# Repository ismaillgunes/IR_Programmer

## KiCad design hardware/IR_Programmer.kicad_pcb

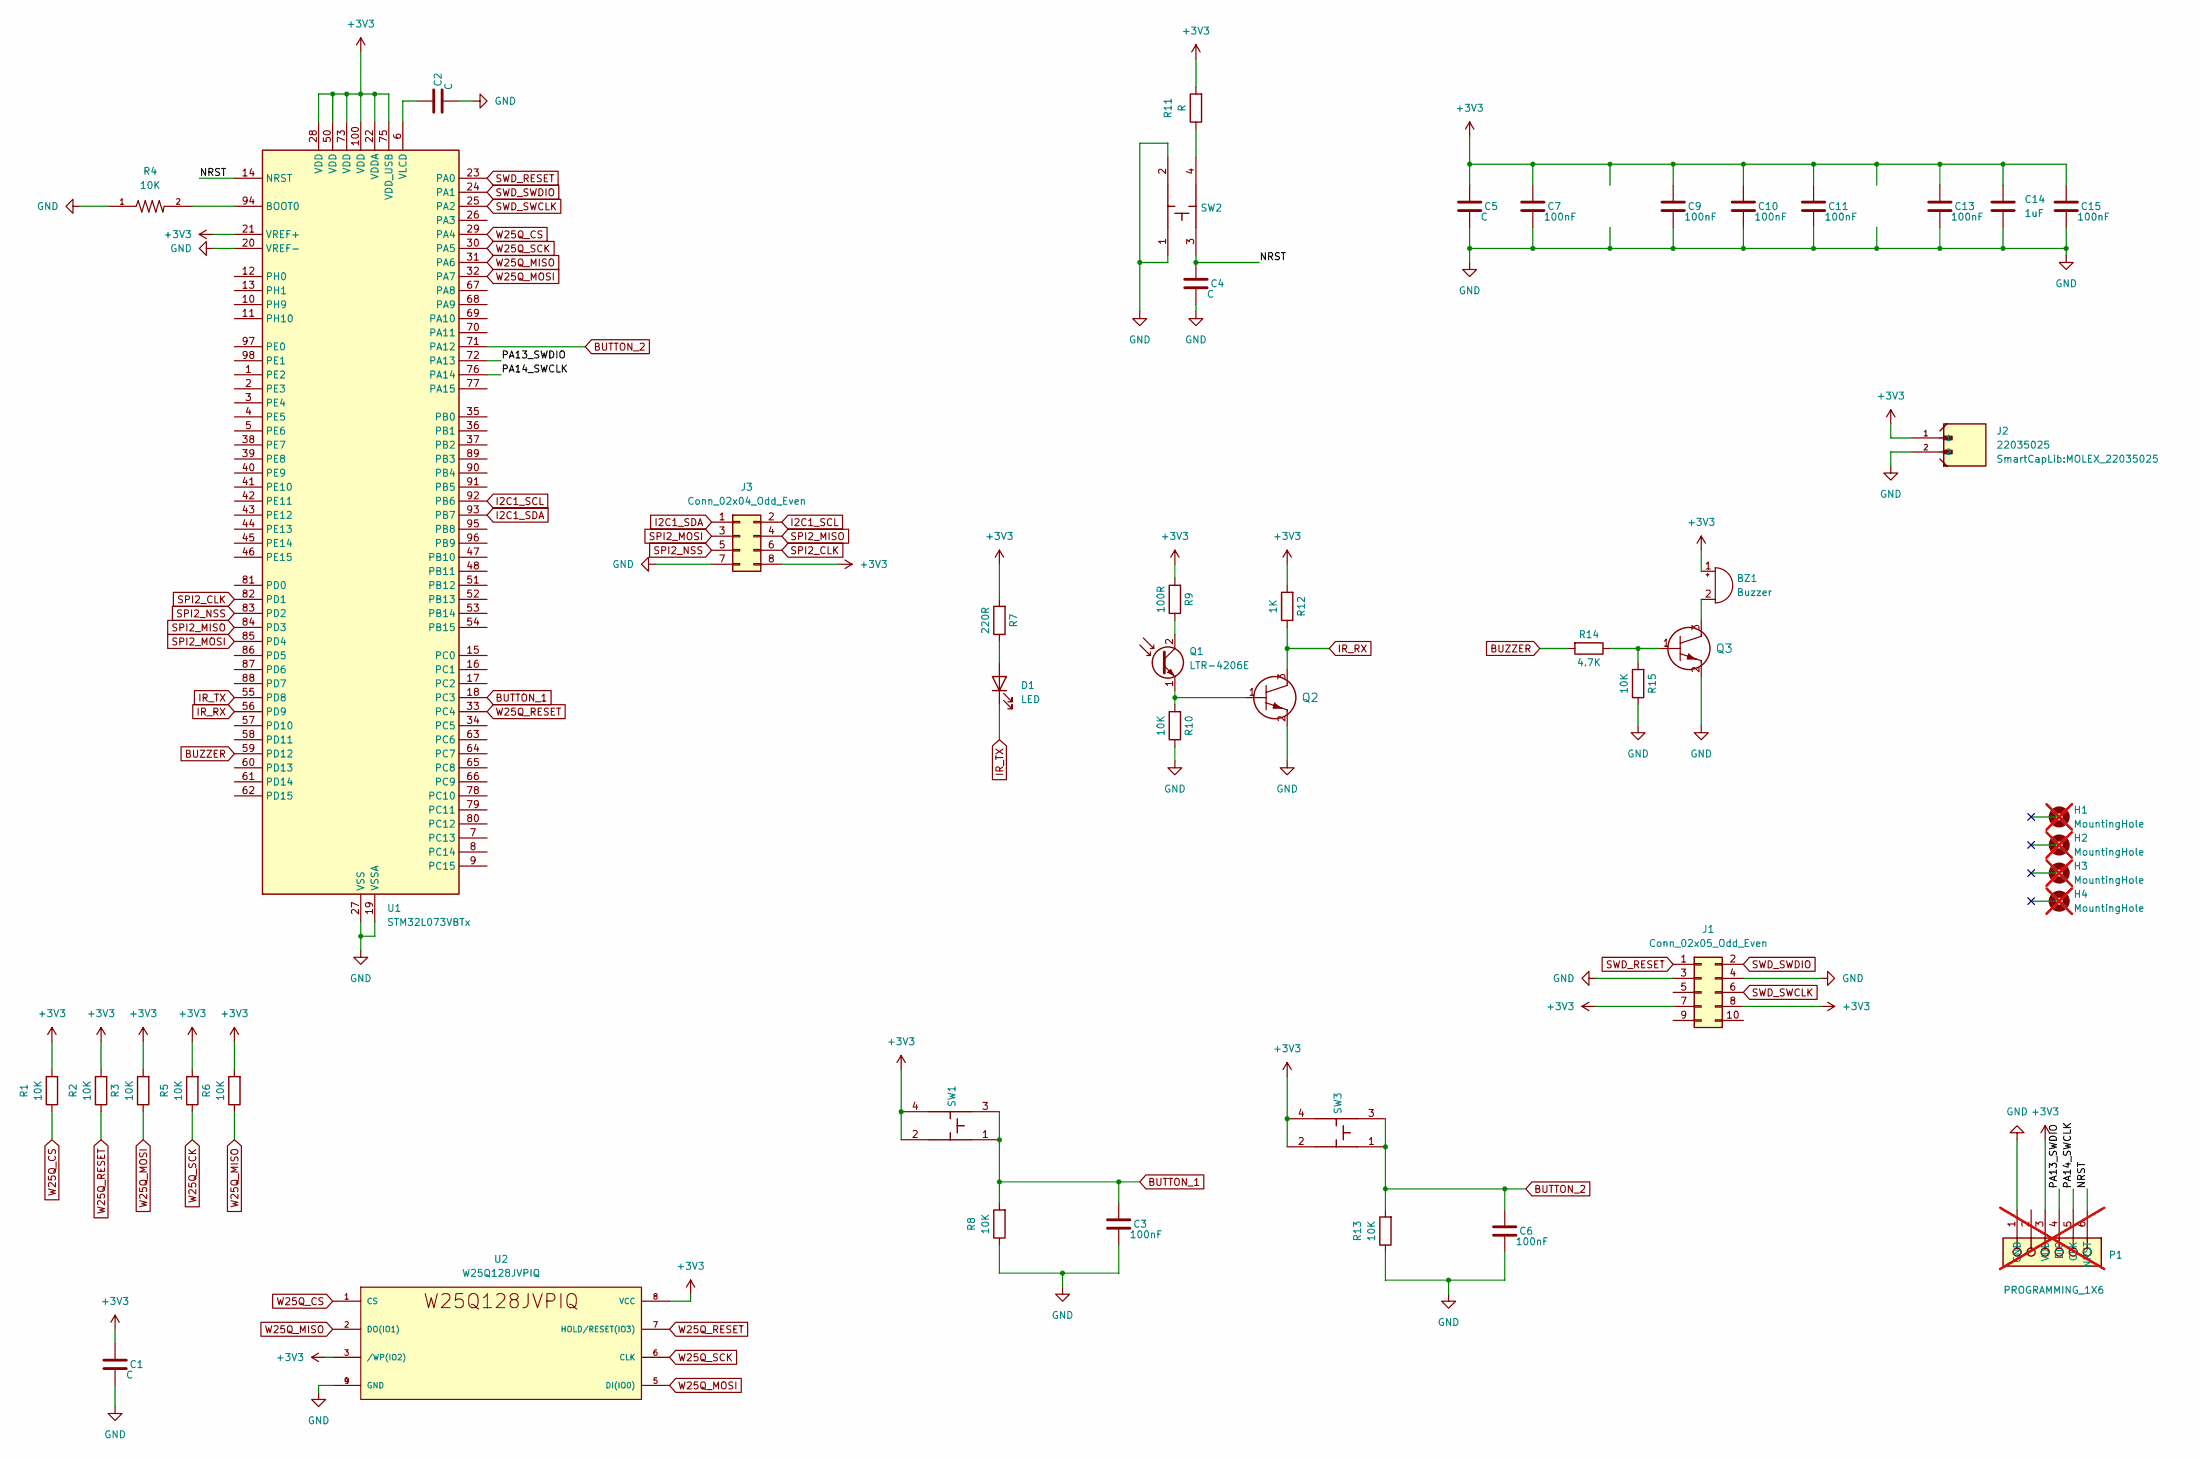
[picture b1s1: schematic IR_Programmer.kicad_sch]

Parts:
BZ1: Buzzer; Buzzer_12x9.5RM7.6
C1, C2, C4: C; C_0603_1608Metric; Manufacturer Part Num. CC0603KRX7R9BB104
C3, C6, C7, C9, C10, C11, C13, C15: 100nF; C_0603_1608Metric; Manufacturer Part Num. CC0603KRX7R9BB104
C5: C; C_0603_1608Metric; Manufacturer Part Num. CL10A106MQ8NNNC
C14: 1uF; C_0603_1608Metric; Manufacturer Part Number CC0603KRX7R7BB105
D1: LED; D_T-1_P2.54mm_Vertical_AnodeUp
H1, H2, H3, H4: MountingHole; MountingHole_3.5mm_Pad; not fitted
J1: Conn_02x05_Odd_Even; PinHeader_2x05_P2.54mm_Vertical
J2: 22035025; MOLEX_22035025; PARTREV A
J3: Conn_02x04_Odd_Even; PinHeader_2x04_P2.54mm_Vertical
P1: PROGRAMMING_1X6; Programming Connection; not fitted
Q1: LTR-4206E; D_T-1_P2.54mm_Vertical_AnodeUp
Q2, Q3: MMBT3904-TP; SOT-23-3
R1, R2, R3, R5, R6, R8, R10, R13, R15: 10K; R_0603_1608Metric; Manufacturer Part Num. RC0603FR-0710KL
R4: 10K; RESC1607X60N
R7: 220R; R_0603_1608Metric; Manufacturer Part Num. RC0603FR-07220RL
R9: 100R; R_0603_1608Metric; Manufacturer Part Num. RC0603FR-07100RL
R11: R; R_0603_1608Metric; Manufacturer Part Num. RC0603FR-0710KL
R12: 1K; R_0603_1608Metric; Manufacturer Part Num. RC0603FR-071KL
R14: 4.7K; R_0603_1608Metric; Manufacturer Part Num. RC0603FR-074K7L
SW1, SW3: DS1042-03-1-8-KKR-160-10; MANUFACTURER PART NUMBER DS1042-03-1-8-KKR-160-10
SW2: DS1042-07-1-1KRR16008; SW_TS24-62-14-BL-200-SMT-TR-67; CURRENT RATING 50mA; MANUFACTURER PART NUMBER DS1042-07-1-1KRR16008
U1: STM32L073VBTx; LQFP-100_14x14mm_P0.5mm
U2: W25Q128JVPIQ; Manufacturer Part Num. W25Q128JVPIQ

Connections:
+3V3: BZ1.1 (+), C1.1, C5.1, C7.1, C9.1, C10.1, C11.1, C13.1, C14.1, C15.1, J1.7, J1.8, J2.1, J3.8, P1.3 (VDD), R1.2, R2.2, R3.2, R5.2, R6.2, R7.2, R9.2, R11.2, R12.2, SW1.2, SW1.4, SW3.2, SW3.4, U1.21 (VREF+), U1.22 (VDDA), U1.28 (VDD), U1.50 (VDD), U1.73 (VDD), U1.75 (VDD_USB), U1.100 (VDD), U2.3 (/WP(IO2)), U2.8 (VCC)
/NRST: C4.1, P1.6 (NRST), SW2.3, U1.14 (NRST)
/PA13_SWDIO: P1.4 (DIO), U1.72 (PA13)
/PA14_SWCLK: P1.5 (CLK), U1.76 (PA14)
BUTTON_1: C3.1, R8.2, SW1.1, SW1.3, U1.18 (PC3)
BUTTON_2: C6.1, R13.2, SW3.1, SW3.3, U1.71 (PA12)
BUZZER: R14.2, U1.59 (PD12)
GND: C1.2, C2.2, C3.2, C4.2, C5.2, C6.2, C7.2, C9.2, C10.2, C11.2, C13.2, C14.2, C15.2, J1.3, J1.4, J2.2, J3.7, P1.1 (GND), Q2.2, Q3.2, R4.1, R8.1, R10.1, R13.1, R15.1, SW2.1, SW2.2, U1.19 (VSSA), U1.20 (VREF-), U1.27 (VSS), U1.49 (VSS), U1.74 (VSS), U1.99 (VSS), U2.4 (GND), U2.9 (GND)
I2C1_SCL: J3.2, U1.92 (PB6)
I2C1_SDA: J3.1, U1.93 (PB7)
IR_RX: Q2.3, R12.1, U1.56 (PD9)
IR_TX: D1.1 (K), U1.55 (PD8)
unnamed: BZ1.2 (-), Q3.3
unnamed: D1.2 (A), R7.1
unnamed: Q1.2 (C), R9.1
unnamed: Q1.1 (E), Q2.1, R10.2
unnamed: Q3.1, R14.1, R15.2
unnamed: R11.1, SW2.4
unnamed: R4.2, U1.94 (BOOT0)
unnamed: C2.1, U1.6 (VLCD)
SPI2_CLK: J3.6, U1.82 (PD1)
SPI2_MISO: J3.4, U1.84 (PD3)
SPI2_MOSI: J3.3, U1.85 (PD4)
SPI2_NSS: J3.5, U1.83 (PD2)
SWD_RESET: J1.1, U1.23 (PA0)
SWD_SWCLK: J1.6, U1.25 (PA2)
SWD_SWDIO: J1.2, U1.24 (PA1)
W25Q_CS: R1.1, U1.29 (PA4), U2.1 (CS)
W25Q_MISO: R6.1, U1.31 (PA6), U2.2 (DO(IO1))
W25Q_MOSI: R3.1, U1.32 (PA7), U2.5 (DI(IO0))
W25Q_RESET: R2.1, U1.33 (PC4), U2.7 (HOLD/RESET(IO3))
W25Q_SCK: R5.1, U1.30 (PA5), U2.6 (CLK)

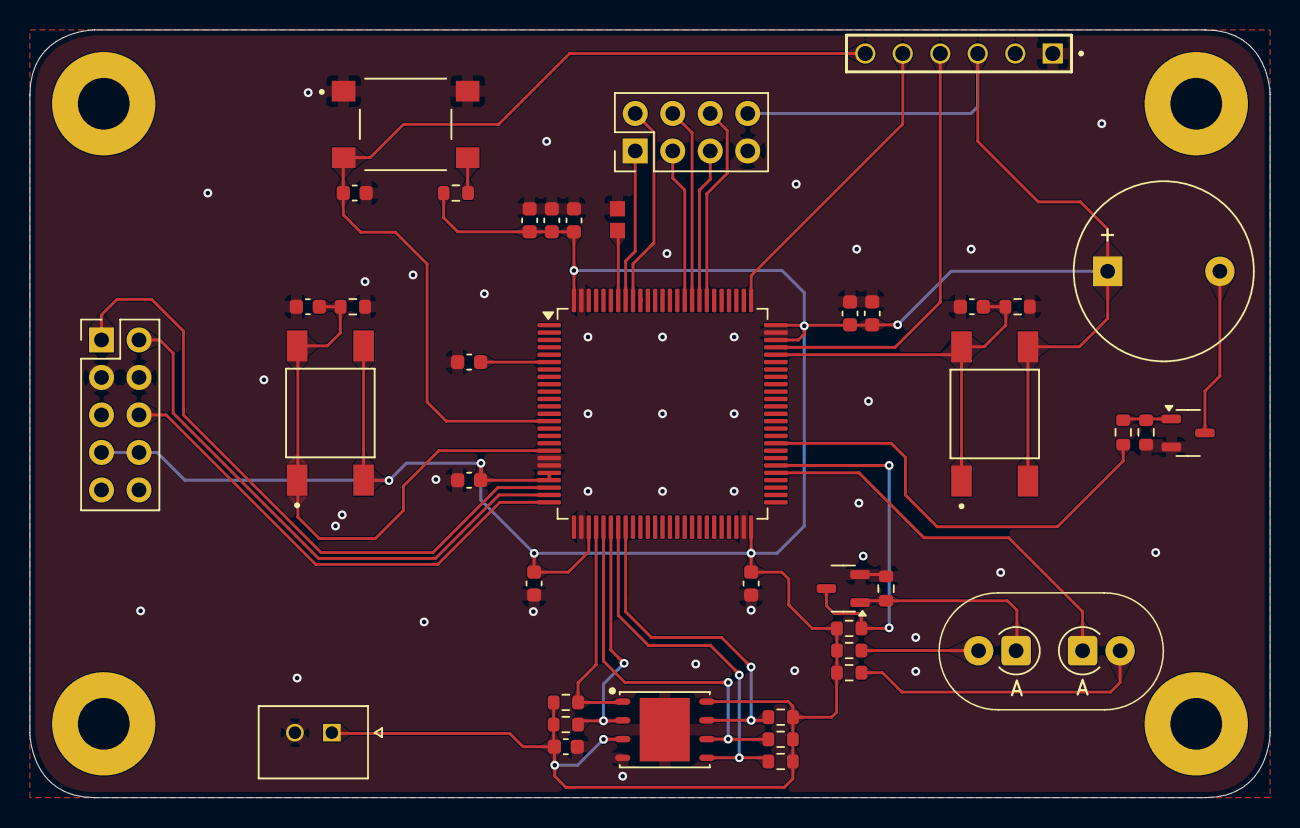
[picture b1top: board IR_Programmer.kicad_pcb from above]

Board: 2 copper layers, 84.0 x 52.0 mm, 46 parts (0 on the bottom side), 32 nets.

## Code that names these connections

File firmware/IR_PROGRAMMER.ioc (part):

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Mcu.Name=STM32L073V(B-Z)Tx
Mcu.Package=LQFP100
Mcu.UserName=STM32L073VBTx
PA0.GPIOParameters=GPIO_Label
PA0.GPIO_Label=SWD_NRST
PA0.Signal=GPIO_Analog
PA1.GPIOParameters=GPIO_Label
PA1.GPIO_Label=SWD_SWDIO
PA1.Signal=GPIO_Analog
PA12.GPIOParameters=GPIO_Label
PA12.GPIO_Label=BtnIR
PA12.Signal=GPIO_Input
PA13.Mode=Serial_Wire
PA13.Signal=SYS_SWDIO
PA14.Mode=Serial_Wire
PA14.Signal=SYS_SWCLK
PA2.GPIOParameters=GPIO_Label
PA2.GPIO_Label=SWD_SWCLK
PA2.Signal=GPIO_Analog
PA4.GPIOParameters=PinState,GPIO_Label
PA4.GPIO_Label=W25Q_CS
PA4.PinState=GPIO_PIN_SET
PA4.Signal=GPIO_Output
PB6.GPIOParameters=GPIO_Speed
PB6.GPIO_Speed=GPIO_SPEED_FREQ_VERY_HIGH
PB6.Mode=Asynchronous
PB6.Signal=USART1_TX
PB7.GPIOParameters=GPIO_Speed,GPIO_PuPd
PB7.GPIO_PuPd=GPIO_PULLUP
PB7.GPIO_Speed=GPIO_SPEED_FREQ_VERY_HIGH
PB7.Mode=Asynchronous
PB7.Signal=USART1_RX
PC3.GPIOParameters=GPIO_Label
PC3.GPIO_Label=BtnSWD
PC3.Signal=GPIO_Input
PC4.GPIOParameters=PinState,GPIO_Label
PC4.GPIO_Label=W25Q_RESET
PC4.PinState=GPIO_PIN_SET
PC4.Signal=GPIO_Output
PD12.GPIOParameters=PinState,GPIO_Label
PD12.GPIO_Label=Buzzer_Pin
PD12.PinState=GPIO_PIN_RESET
PD12.Signal=GPIO_Output
PD8.GPIOParameters=GPIO_Speed
PD8.GPIO_Speed=GPIO_SPEED_FREQ_VERY_HIGH
PD8.Mode=Asynchronous
PD8.Signal=LPUART1_TX
PD9.GPIOParameters=GPIO_Speed
PD9.GPIO_Speed=GPIO_SPEED_FREQ_VERY_HIGH
PD9.Mode=Asynchronous
PD9.Signal=LPUART1_RX
RCC.HSE_VALUE=8000000
RCC.SYSCLKFreq_VALUE=16000000
RCC.SYSCLKSource=RCC_SYSCLKSOURCE_HSI
board=custom

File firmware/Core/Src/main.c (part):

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  *  IR_Programmer_PPM karti (STM32L073VBT) uzerinde calisir. fw_image.h icindeki
  *  firmware'i hedef STM32L0'a iki yoldan biriyle yazar:
  *
  *    - IR  : SW3 / BUTTON_2 (PA12) -> hedefin sistem bootloader'i (AN3155),
  *            LPUART1 (PD8 = TX, PD9 = RX)
  *    - SWD : SW1 / BUTTON_1 (PC3)  -> bit-bang SWD (SWD/swd.c), J1 konnektoru
  *            (PA2 = SWCLK, PA1 = SWDIO, PA0 = NRST)
  *    - Log    : USART1 (PB6 = TX, PB7 = RX) <- J3, PC'ye 115200 8N1 log
  *    - Buzzer : PD12 (Q3) - kartta LCD yok, geri bildirim bip ile
  ******************************************************************************
  */
/* USER CODE END Header */
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/* USER CODE BEGIN 0 */

/* ============================================================
 *  Buzzer (PD12 -> Q3) - aktif buzzer, ms suresince oter
 * ============================================================ */
void Buzzer(uint16_t ms)
{
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  __HAL_RCC_GPIOB_CLK_ENABLE();

  /*Configure GPIO pin Output Level */
  HAL_GPIO_WritePin(W25Q_CS_GPIO_Port, W25Q_CS_Pin, GPIO_PIN_SET);

  /*Configure GPIO pin Output Level */
  HAL_GPIO_WritePin(W25Q_RESET_GPIO_Port, W25Q_RESET_Pin, GPIO_PIN_SET);

  /*Configure GPIO pin Output Level */
  HAL_GPIO_WritePin(Buzzer_Pin_GPIO_Port, Buzzer_Pin_Pin, GPIO_PIN_RESET);
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  GPIO_InitStruct.Pull = GPIO_NOPULL;
  HAL_GPIO_Init(BtnSWD_GPIO_Port, &GPIO_InitStruct);

  /*Configure GPIO pins : SWD_NRST_Pin SWD_SWDIO_Pin SWD_SWCLK_Pin */
  GPIO_InitStruct.Pin = SWD_NRST_Pin|SWD_SWDIO_Pin|SWD_SWCLK_Pin;
  GPIO_InitStruct.Mode = GPIO_MODE_ANALOG;
  GPIO_InitStruct.Pull = GPIO_NOPULL;
  HAL_GPIO_Init(GPIOA, &GPIO_InitStruct);

  /*Configure GPIO pin : W25Q_CS_Pin */
  GPIO_InitStruct.Pin = W25Q_CS_Pin;
  GPIO_InitStruct.Mode = GPIO_MODE_OUTPUT_PP;
  GPIO_InitStruct.Pull = GPIO_NOPULL;
  GPIO_InitStruct.Speed = GPIO_SPEED_FREQ_LOW;
  HAL_GPIO_Init(W25Q_CS_GPIO_Port, &GPIO_InitStruct);

  /*Configure GPIO pin : W25Q_RESET_Pin */
  GPIO_InitStruct.Pin = W25Q_RESET_Pin;
  GPIO_InitStruct.Mode = GPIO_MODE_OUTPUT_PP;
  GPIO_InitStruct.Pull = GPIO_NOPULL;
  GPIO_InitStruct.Speed = GPIO_SPEED_FREQ_LOW;
  HAL_GPIO_Init(W25Q_RESET_GPIO_Port, &GPIO_InitStruct);

  /*Configure GPIO pin : Buzzer_Pin_Pin */
  GPIO_InitStruct.Pin = Buzzer_Pin_Pin;
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
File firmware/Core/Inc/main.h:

/* USER CODE BEGIN Header */
/**
  ******************************************************************************
  * @file           : main.h
  * @brief          : Header for main.c file.
  *                   IR Programmer (IR_Programmer_PPM karti: STM32L073VBT + IR + buzzer)
  ******************************************************************************
  * @attention
  *
  * Bu yazilim, IR uzerinden hedef STM32'nin sistem bootloader'ina (AN3155)
  * baglanip fw_image.h icindeki firmware'i yazar.
  *   - IR linki : LPUART1 (PD8 = IR_TX -> D1 katot, PD9 = IR_RX <- Q2 kollektor)
  *   - SWD      : J1 (PA2 = SWCLK, PA1 = SWDIO, PA0 = NRST) - SWD/inc/swd.h
  *   - Log      : USART1  (PB6 = TX -> J3 pin2, PB7 = RX <- J3 pin1)
  *   - Geri bildirim: buzzer (PD12, Q3 uzerinden) - kartta LCD yok
  *
  ******************************************************************************
  */
/* USER CODE END Header */

/* Define to prevent recursive inclusion -------------------------------------*/
#ifndef __MAIN_H
#define __MAIN_H

#ifdef __cplusplus
extern "C" {
#endif

/* Includes ------------------------------------------------------------------*/
#include "stm32l0xx_hal.h"

/* Private includes ----------------------------------------------------------*/
/* USER CODE BEGIN Includes */
/* USER CODE END Includes */

/* Exported types ------------------------------------------------------------*/
/* USER CODE BEGIN ET */

/* USER CODE END ET */

/* Exported constants --------------------------------------------------------*/
/* USER CODE BEGIN EC */

/* USER CODE END EC */

/* Exported macro ------------------------------------------------------------*/
/* USER CODE BEGIN EM */

/* USER CODE END EM */

/* Exported functions prototypes ---------------------------------------------*/
void Error_Handler(void);

/* USER CODE BEGIN EFP */
void Buzzer(uint16_t ms);
void Buzzer_Tick(void);   /* SysTick'ten 1 ms'de bir cagrilir (mesgul bipi) */
/* USER CODE END EFP */

/* Private defines -----------------------------------------------------------*/
#define BtnSWD_Pin GPIO_PIN_3
#define BtnSWD_GPIO_Port GPIOC
#define SWD_NRST_Pin GPIO_PIN_0
#define SWD_NRST_GPIO_Port GPIOA
#define SWD_SWDIO_Pin GPIO_PIN_1
#define SWD_SWDIO_GPIO_Port GPIOA
#define SWD_SWCLK_Pin GPIO_PIN_2
#define SWD_SWCLK_GPIO_Port GPIOA
#define W25Q_CS_Pin GPIO_PIN_4
#define W25Q_CS_GPIO_Port GPIOA
#define W25Q_RESET_Pin GPIO_PIN_4
#define W25Q_RESET_GPIO_Port GPIOC
#define Buzzer_Pin_Pin GPIO_PIN_12
#define Buzzer_Pin_GPIO_Port GPIOD
#define BtnIR_Pin GPIO_PIN_12
#define BtnIR_GPIO_Port GPIOA

/* USER CODE BEGIN Private defines */
extern UART_HandleTypeDef hlpuart1; /* IR linki  (LPUART1 / PD8-PD9) */
extern UART_HandleTypeDef huart1;   /* Log       (USART1  / PB6-PB7) */
/* USER CODE END Private defines */

#ifdef __cplusplus
}
#endif

#endif /* __MAIN_H */
